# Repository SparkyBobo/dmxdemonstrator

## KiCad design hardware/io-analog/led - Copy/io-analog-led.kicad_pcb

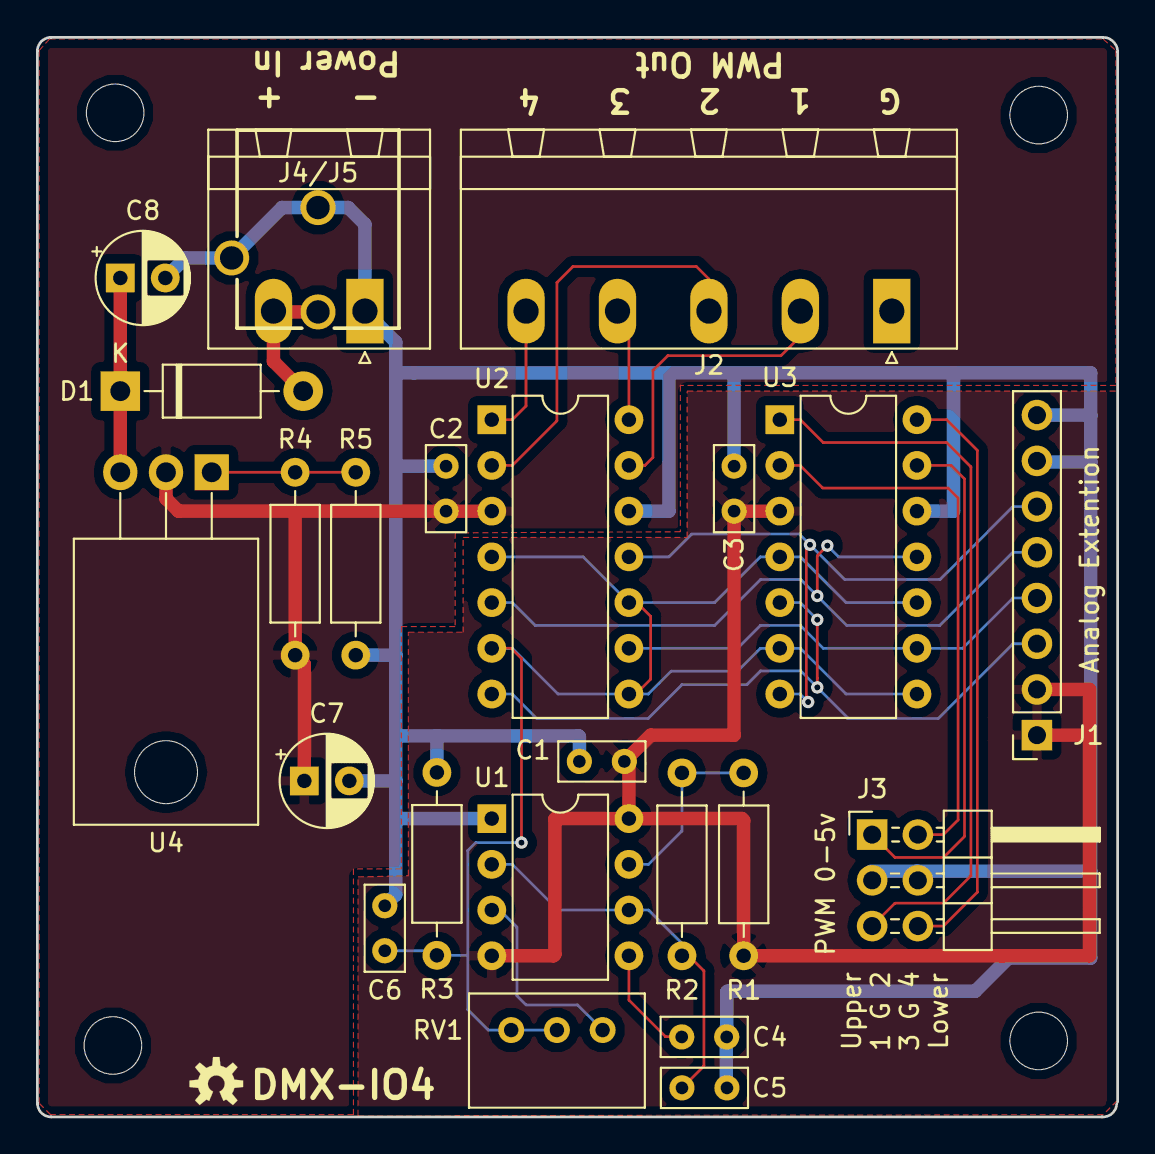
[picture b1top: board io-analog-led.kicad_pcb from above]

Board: 2 copper layers, 60.0 x 60.0 mm, 28 parts (0 on the bottom side), 23 nets.

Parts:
C1, C2, C3: 0.1uF; C_Rect_L4.6mm_W2.0mm_P2.50mm_MKS02_FKP02
C4: 100nf; C_Rect_L4.6mm_W2.0mm_P2.50mm_MKS02_FKP02
C5, C6: 0.68uF; C_Rect_L4.6mm_W2.0mm_P2.50mm_MKS02_FKP02
C7, C8: 10uF; CP_Radial_D5.0mm_P2.50mm
D1: 1N5819; D_DO-41_SOD81_P10.16mm_Horizontal
J1: Analog Extension; PinSocket_1x08_P2.54mm_Vertical
J2: Vo Output; PhoenixContact_MSTBA_2,5_5-G-5,08_1x05_P5.08mm_Horizontal
J3: +5V Output; PinHeader_2x03_P2.54mm_Horizontal
J4: Power; PhoenixContact_MSTBA_2,5_2-G-5,08_1x02_P5.08mm_Horizontal
J5: Power; POWER_JACK_PTH_BREAD
MH1, MH2, MH3, MH4: MountingHole; MountingHole_3.2mm_M3
R1: 330; R_Axial_DIN0207_L6.3mm_D2.5mm_P10.16mm_Horizontal
R2, R3: 10k; R_Axial_DIN0207_L6.3mm_D2.5mm_P10.16mm_Horizontal
R4: 392 1%; R_Axial_DIN0207_L6.3mm_D2.5mm_P10.16mm_Horizontal
R5: 2.74k 1%; R_Axial_DIN0207_L6.3mm_D2.5mm_P10.16mm_Horizontal
RV1: 10k; Potentiometer_Bourns_3299W_Vertical
U1: LM555; DIP-8_W7.62mm
U2, U3: LM339; DIP-14_W7.62mm
U4: LM317T; TO-220-3_Horizontal_TabDown

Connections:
+5V: C1.1, C3.1, J1.1, J1.2, R1.1, U1.4, U1.8, U3.3
/AO0: J1.6, U2.11, U3.7
/AO1: J1.5, U2.5, U3.11
/AO2: J1.4, U2.9, U3.9
/AO3: J1.3, U2.7, U3.5
GND: C1.2, C2.2, C3.2, C4.1, C5.1, C6.2, C7.2, C8.2, J1.7, J1.8, J2.1, J3.3, J3.4, J4.1, J5.GND, J5.GNDB, R3.1, R5.1, U1.1, U2.12, U3.12
unnamed: C2.1, C7.1, R4.2, U2.3, U4.2
unnamed: C4.2, U1.5
unnamed: C5.2, R2.2, U1.2, U1.6
unnamed: C6.1, R3.2, RV1.2, RV1.3, U2.4, U2.6, U2.8, U2.10, U3.4, U3.6, U3.8, U3.10
unnamed: C8.1, D1.1, U4.3
unnamed: D1.2, J4.2, J5.PWR
unnamed: J2.2, U2.13
unnamed: J2.3, U2.2
unnamed: J2.4, U2.14
unnamed: J2.5, U2.1
unnamed: J3.1, U3.13
unnamed: J3.2, U3.2
unnamed: J3.5, U3.1
unnamed: J3.6, U3.14
unnamed: R1.2, R2.1, U1.7
unnamed: R4.1, R5.2, U4.1
unnamed: RV1.1, U1.3

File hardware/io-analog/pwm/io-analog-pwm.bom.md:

# Bill Of Materials (BOM)

## Schematic

**Filename:** E:\OpenSource\dmxdemonstrator\hardware\io-analog\pwm\io-analog-pwm.sch

**Date Modified:** 4/11/2024 8:56:17 PM

**Kicad Version:** Eeschema (5.1.12)-1

**Component Count:** 25

## Components

Item#|Quantity|Reference|Description|Manufacturer|Part Number|Datasheet|Notes
-----|--------|---------|-----------|------------|-----------|---------|-----
1|1|PCB|Analog IO PWM PCB|OHSPark|DMX-IO4, Rev 1.4||[Order](https://oshpark.com/shared_projects/xqcuVAnE)|
2|3|C1, C2, C3|0.1uF||||
3|2|C4, C5|0.68uF||||
4|2|C6, C7|10uF||||
5|1|D1|Schottky Diode, 40V 1A|Vishay General Semiconductor|1N5819|[Data Sheet](http://www.vishay.com/docs/88525/1n5817.pdf)|
6|1|J1|0.1 Female header, stacking||||
7|1|J2|Screw Terminal, 5 pin, 3.81 pitch|Phoenix Contact|1803303||
8|1|J2|Screw Terminal Plug, 5 pin, 3.81 pitch|Phoenix Contact|1840395||
9|1|J3|2x3-pin right-angle header||||
10|1|J4|Screw Terminal, 2 pin, 3.81 pitch|Phoenix Contact|1803277||
11|1|J4|Screw Terminal Plug, 2 pin, 3.81 pitch|Phoenix Contact|1803578||
12|1|R1|330 ohm||||
13|2|R2, R3|10k  ohm||||
14|1|R4|392 ohm 1% resistor||||
15|1|R5|2.74k 1% resistor||||
16|1|RV1|10k trimmer pot|Bourns|3299P-1-103LF|[Data Sheet](https://www.bourns.com/docs/Product-Datasheets/3299.pdf)|
17|1|U1|555 Precision Timer|Texas Instruments|NE555|[Data Sheet](https://www.ti.com/lit/ds/symlink/ne555.pdf)|
18|1|U2|Quad Differential Comparator|Texas Instruments|LM339|[Data Sheet](http://www.ti.com/lit/ds/symlink/lm339.pdf)|
19|1|U3|Linear Regulator, Adjustable, 1.5A TO220AB|STMicroelectronics|LM317T|[Data Sheet](http://www.st.com/content/ccc/resource/technical/document/da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|
<!--BOMROW-->

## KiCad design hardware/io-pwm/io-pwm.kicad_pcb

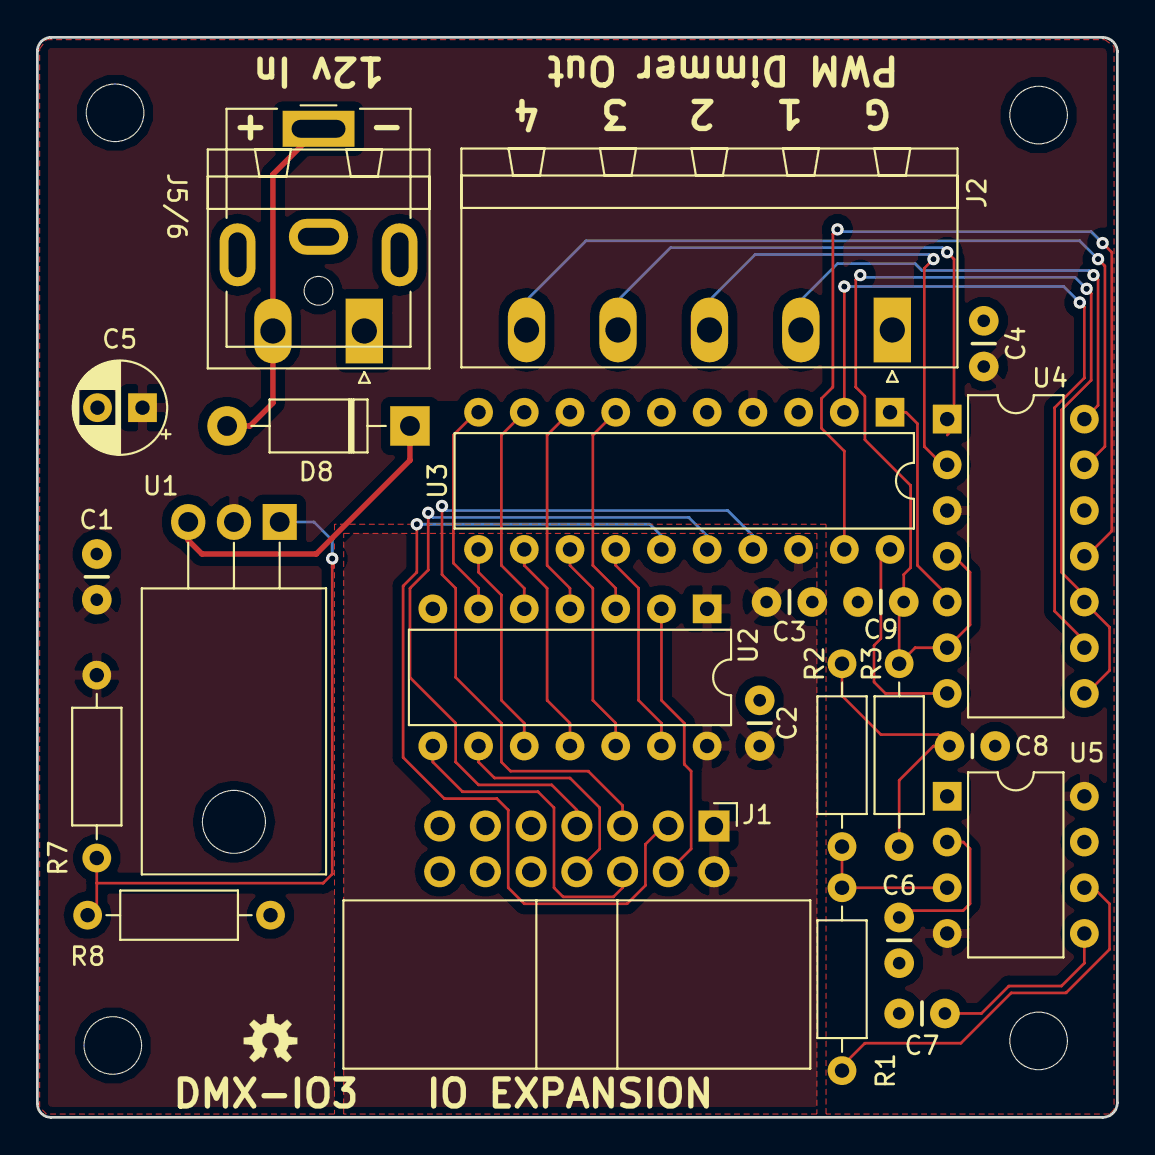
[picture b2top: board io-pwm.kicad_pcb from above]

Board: 2 copper layers, 60.0 x 60.0 mm, 28 parts (0 on the bottom side), 34 nets.

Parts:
C1, C2, C3, C4: .01uF; CAP-PTH-2.54
C5: 10uF; CP_Radial_D5.0mm_P2.50mm
C6, C8, C9: 10nf; CAP-PTH-2.54
C7: 100nf; CAP-PTH-2.54
D8: 1N5819; D_DO-41_SOD81_P10.16mm_Horizontal
J1: IO EXTENSION; IDC-Header_2x07_P2.54mm_Horizontal
J2: PWM_OUT; PhoenixContact_MSTBA_2,5_5-G-5,08_1x05_P5.08mm_Horizontal
J5: 12V_A; BarrelJack_CUI_PJ-063AH_Horizontal
J6: 12V_B; PhoenixContact_MSTBA_2,5_2-G-5,08_1x02_P5.08mm_Horizontal
MH1, MH2, MH3, MH4: MountingHole; MountingHole_3.2mm_M3
R1: 10k; R_Axial_DIN0207_L6.3mm_D2.5mm_P10.16mm_Horizontal
R2, R3: 1k; R_Axial_DIN0207_L6.3mm_D2.5mm_P10.16mm_Horizontal
R7: 390; R_Axial_DIN0207_L6.3mm_D2.5mm_P10.16mm_Horizontal
R8: 2.7k; R_Axial_DIN0207_L6.3mm_D2.5mm_P10.16mm_Horizontal
U1: LM317T; TO-220-3_Horizontal_TabDown
U2: 74LS164; DIP-14_W7.62mm
U3: TLC7226A; DIP-20_W7.62mm
U4: LM339; DIP-14_W7.62mm
U5: LM555; DIP-8_W7.62mm

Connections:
+5V: C2.1, C3.1, J1.1, J1.2, U2.1, U2.14, U3.18
+10V: C1.1, C4.1, C5.1, R7.2, U1.2, U3.4, U4.3, U5.4, U5.8
/A0: J1.5, U3.17
/A1: J1.7, U3.16
/AO0: U3.2, U4.9
/AO1: U3.1, U4.5
/AO2: U3.20, U4.7
/AO3: U3.19, U4.11
/D0: U2.13, U3.14
/D1: U2.12, U3.13
/D2: U2.11, U3.12
/D3: U2.10, U3.11
/D4: U2.6, U3.10
/D5: U2.5, U3.9
/D6: U2.4, U3.8
/D7: U2.3, U3.7
/SR-CLK: J1.6, U2.8
/SR-OUT: J1.4, U2.2
/~SR_CLR: J1.8, U2.9
/~WR: J1.3, U3.15
GND: C1.2, C2.2, C3.2, C4.2, C5.2, C6.1, C7.1, C8.2, C9.2, J1.13, J1.14, J2.1, J5.2, J6.1, R8.1, U2.7, U3.3, U3.5, U3.6, U4.12, U5.1
unnamed: C6.2, U5.2
unnamed: C7.2, U5.5
unnamed: C8.1, R2.1, R3.2
unnamed: C9.1, R3.1, U4.4, U4.6, U4.8, U4.10
unnamed: D8.1, U1.3
unnamed: D8.2, J5.1, J6.2
unnamed: J2.2, U4.14
unnamed: J2.3, U4.2
unnamed: J2.4, U4.1
unnamed: J2.5, U4.13
unnamed: R1.1, U5.6
unnamed: R1.2, R2.2, U5.3
unnamed: R7.1, R8.2, U1.1

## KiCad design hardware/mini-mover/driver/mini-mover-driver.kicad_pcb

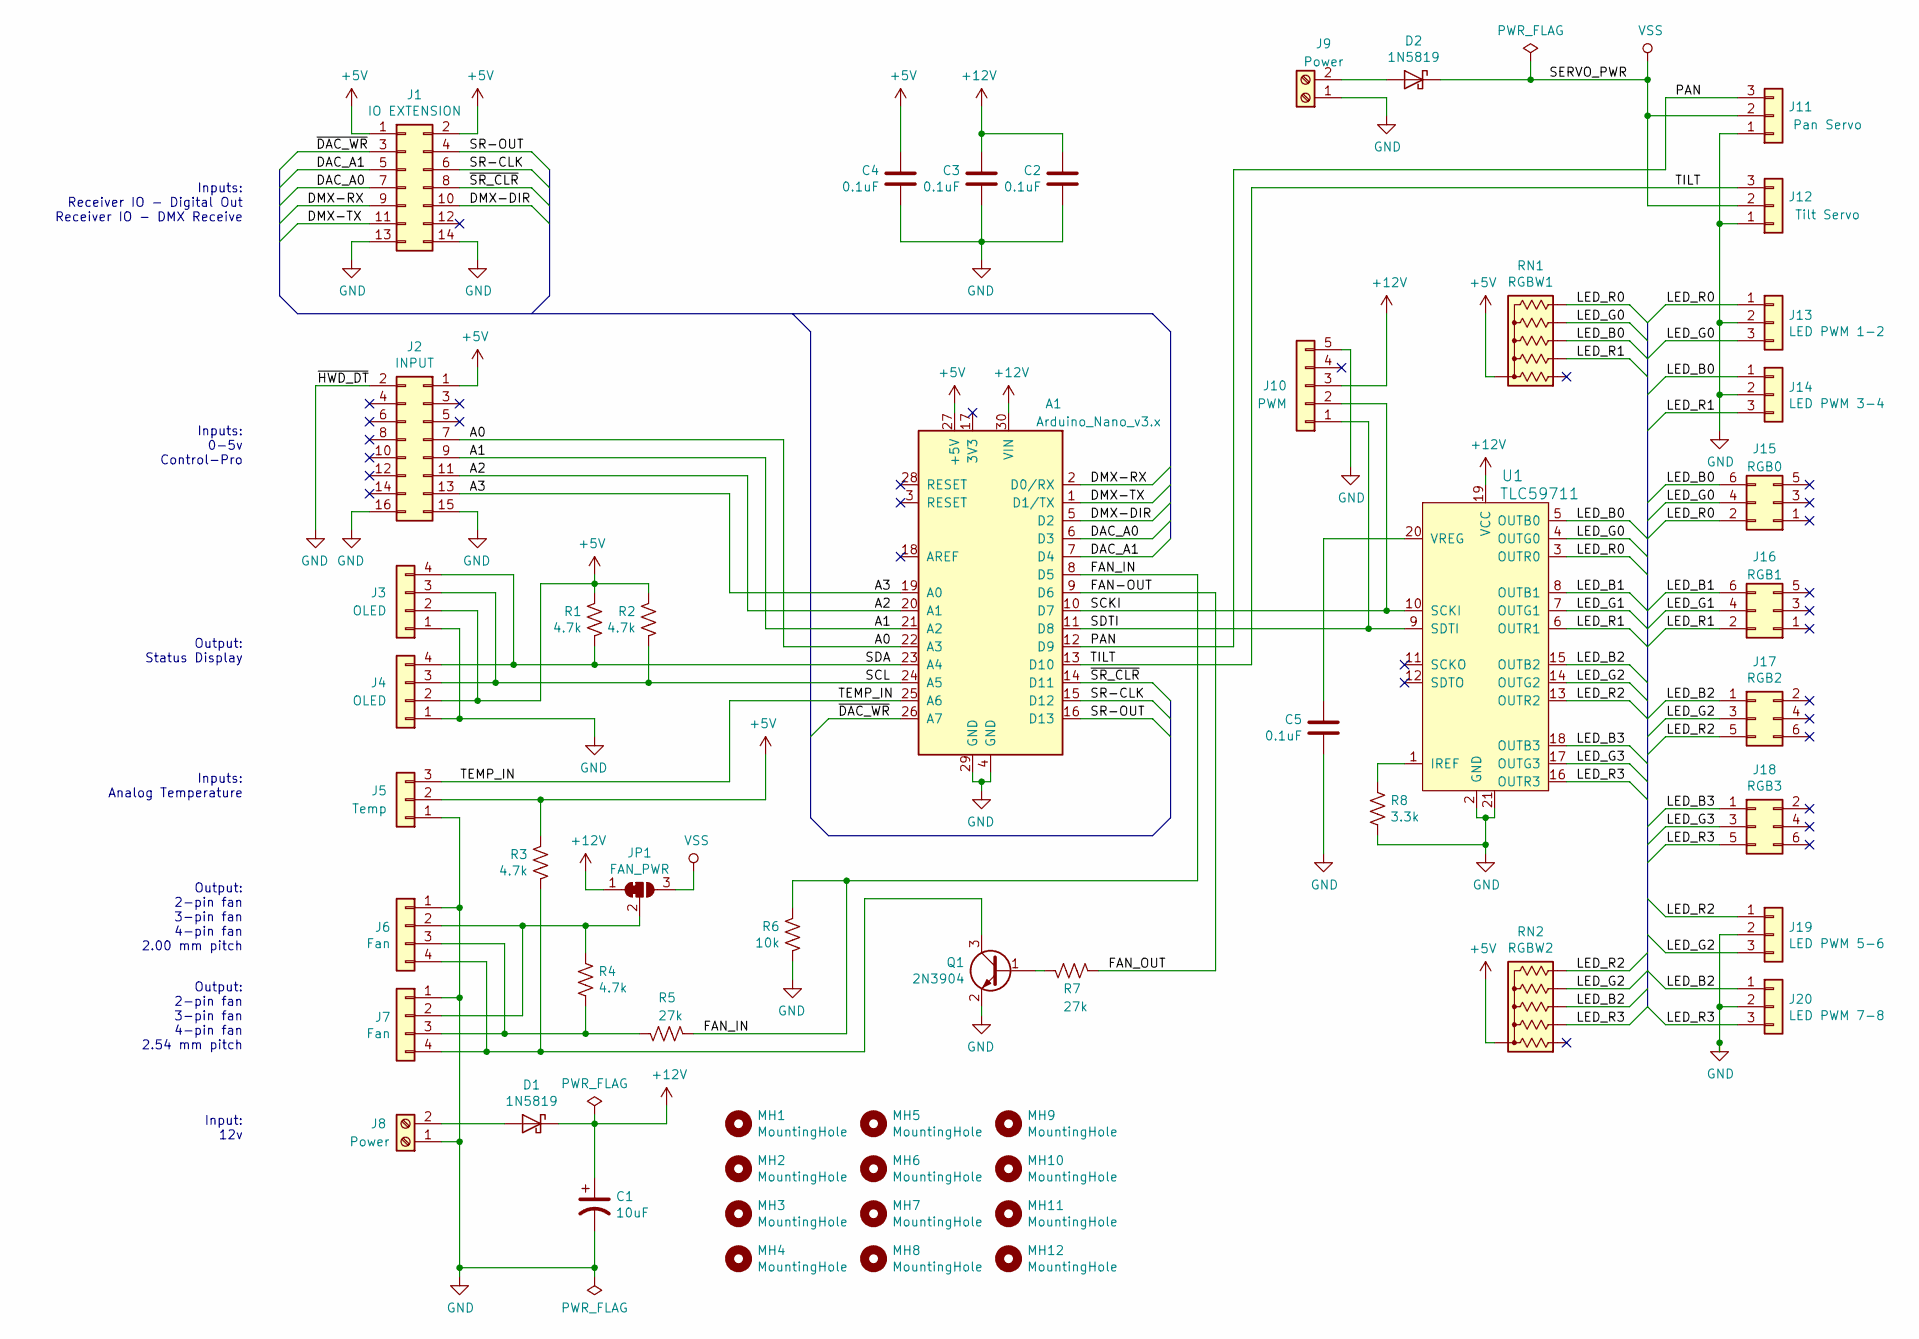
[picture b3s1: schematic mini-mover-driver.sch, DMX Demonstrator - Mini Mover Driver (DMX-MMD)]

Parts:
A1: Arduino_Nano_v3.x; Arduino_Nano
C1: 10uF; CP_Radial_D5.0mm_P2.50mm; Digi-Key_PN P10425CT-ND
C2, C4: 0.1uF; C_Rect_L4.6mm_W2.0mm_P2.50mm_MKS02_FKP02
C3, C5: 0.1uF; C_1206_3216Metric_Pad1.42x1.75mm_HandSolder
D1, D2: 1N5819; D_DO-41_SOD81_P10.16mm_Horizontal; Digi-Key_PN 1N5819-E3/54GITR-ND
J1: IO EXTENSION; IDC-Header_2x07_P2.54mm_Vertical
J2: INPUT; IDC-Header_2x08_P2.54mm_Vertical
J3, J4: OLED; PinHeader_1x04_P2.54mm_Vertical
J5: Temp; PinHeader_1x03_P2.54mm_Vertical
J6: Fan; PinHeader_1x04_P2.00mm_Vertical
J7: Fan; PinHeader_1x04_P2.54mm_Vertical
J8, J9: Power; PhoenixContact_MC_1,5_2-G-3.81_1x02_P3.81mm_Horizontal; Digi-Key_PN 277-1106-ND
J10: PWM; PinHeader_1x05_P2.54mm_Vertical
J11: Pan Servo; PinHeader_1x03_P2.54mm_Vertical
J12: Tilt Servo; PinHeader_1x03_P2.54mm_Vertical
J13: LED PWM 1-2; PinHeader_1x03_P2.54mm_Vertical
J14: LED PWM 3-4; PinHeader_1x03_P2.54mm_Vertical
J15: RGB0; PinHeader_2x03_P2.54mm_Vertical
J16: RGB1; PinHeader_2x03_P2.54mm_Vertical
J17: RGB2; PinHeader_2x03_P2.54mm_Vertical
J18: RGB3; PinHeader_2x03_P2.54mm_Vertical
J19: LED PWM 5-6; PinHeader_1x03_P2.54mm_Vertical
J20: LED PWM 7-8; PinHeader_1x03_P2.54mm_Vertical
JP1: FAN_PWR; SolderJumper-3_P1.3mm_Bridged12_RoundedPad1.0x1.5mm
MH1, MH2, MH3, MH4, MH5, MH6, MH7, MH8: MountingHole; MountingHole_3.2mm_M3
MH9, MH10, MH11, MH12: MountingHole; MountingHole_2.2mm_M2
Q1: 2N3904; TO-92L_HandSolder
R1, R2, R3, R4: 4.7k; R_Axial_DIN0207_L6.3mm_D2.5mm_P10.16mm_Horizontal
R5, R7: 27k; R_Axial_DIN0207_L6.3mm_D2.5mm_P10.16mm_Horizontal
R6: 10k; R_Axial_DIN0207_L6.3mm_D2.5mm_P10.16mm_Horizontal
R8: 3.3k; R_1206_3216Metric_Pad1.42x1.75mm_HandSolder
RN1: RGBW1; R_Array_SIP6
RN2: RGBW2; R_Array_SIP6
U1: TLC59711; TSSOP-20-1EP_W4.4mm; MPN TLC59711PWPR; Digi-Key_PN 296-36745-1-ND

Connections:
+5V: A1.27 (+5V), C4.1, J1.1, J1.2, J2.1, J2.4, J3.2, J4.2, J5.2, R1.1, R2.1, R3.1, RN1.1 (common), RN2.1 (common)
+12V: A1.30 (VIN), C1.1, C2.1, C3.1, D1.1 (K), J10.3, JP1.1 (A), U1.19 (VCC)
/A0: A1.22 (A3), J2.7
/A1: A1.21 (A2), J2.9
/A2: A1.20 (A1), J2.11
/A3: A1.19 (A0), J2.13
/DAC_A0: A1.6 (D3), J1.7
/DAC_A1: A1.7 (D4), J1.5
/DMX-DIR: A1.5 (D2), J1.10
/DMX-RX: A1.2 (D0/RX), J1.9
/DMX-TX: A1.1 (D1/TX), J1.11
/FAN-OUT: A1.9 (D6), R7.1
/FAN_IN: A1.8 (D5), R5.1, R6.1
/LED_B0: J14.1, J15.6, RN1.4 (R3), U1.5 (OUTB0)
/LED_B1: J16.6, U1.8 (OUTB1)
/LED_B2: J17.1, J20.1, RN2.4 (R3), U1.15 (OUTB2)
/LED_B3: J18.1, U1.18 (OUTB3)
/LED_G0: J13.3, J15.4, RN1.5 (R4), U1.4 (OUTG0)
/LED_G1: J16.4, U1.7 (OUTG1)
/LED_G2: J17.3, J19.3, RN2.5 (R4), U1.14 (OUTG2)
/LED_G3: J18.3, U1.17 (OUTG3)
/LED_R0: J13.1, J15.2, RN1.6 (R5), U1.3 (OUTR0)
/LED_R1: J14.3, J16.2, RN1.3 (R2), U1.6 (OUTR1)
/LED_R2: J17.5, J19.1, RN2.6 (R5), U1.13 (OUTR2)
/LED_R3: J18.5, J20.3, RN2.3 (R2), U1.16 (OUTR3)
/PAN: A1.12 (D9), J11.3
/SCKI: A1.10 (D7), J10.2, U1.10 (SCKI)
/SCL: A1.24 (A5), J3.3, J4.3, R2.2
/SDA: A1.23 (A4), J3.4, J4.4, R1.2
/SDTI: A1.11 (D8), J10.1, U1.9 (SDTI)
/SR-CLK: A1.15 (D12), J1.6
/SR-OUT: A1.16 (D13), J1.4
/TEMP_IN: A1.25 (A6), J5.3
/TILT: A1.13 (D10), J12.3
/~DAC_WR: A1.26 (A7), J1.3
/~SR_CLR: A1.14 (D11), J1.8
GND: A1.4 (GND), A1.29 (GND), C1.2, C2.2, C3.2, C4.2, C5.2, J1.13, J1.14, J2.2, J2.8, J2.15, J2.16, J3.1, J4.1, J5.1, J6.1, J7.1, J8.1, J9.1, J10.5, J11.1, J12.1, J13.2, J14.2, J19.2, J20.2, Q1.2 (E), R6.2, R8.2, U1.2 (GND), U1.21
unnamed: C5.1, U1.20 (VREG)
unnamed: D1.2 (A), J8.2
unnamed: D2.2 (A), J9.2
unnamed: J6.2, J7.2, JP1.2 (C), R4.1
unnamed: J6.3, J7.3, R4.2, R5.2
unnamed: J6.4, J7.4, Q1.3 (C), R3.2
unnamed: Q1.1 (B), R7.2
unnamed: R8.1, U1.1 (IREF)
VSS: D2.1 (K), J11.2, J12.2, JP1.3 (B)

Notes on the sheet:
Inputs: Receiver IO - Digital Out Receiver IO - DMX Receive
Inputs: 0-5v Control-Pro
Inputs: Analog Temperature
Output: 2-pin fan 3-pin fan 4-pin fan 2.00 mm pitch
Output: 2-pin fan 3-pin fan 4-pin fan 2.54 mm pitch
Input: 12v
Output: Status Display

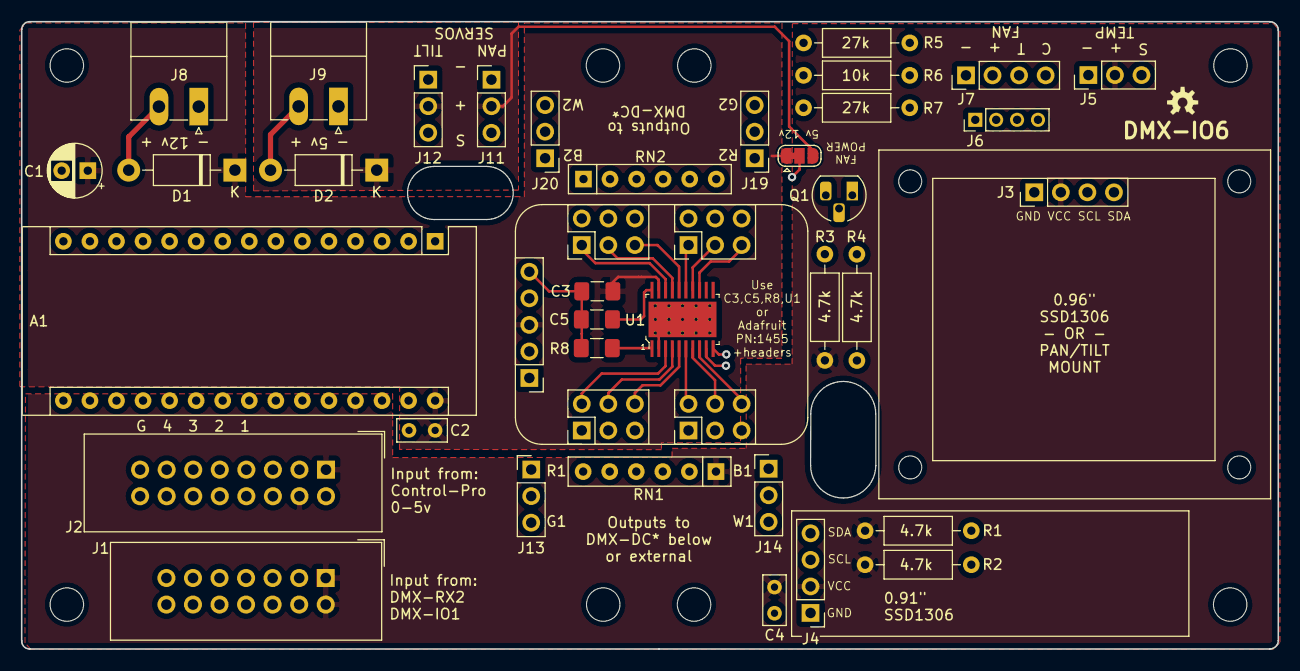
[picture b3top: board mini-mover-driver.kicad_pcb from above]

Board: 4 copper layers, 120.2 x 60.0 mm, 53 parts (0 on the bottom side), 46 nets.

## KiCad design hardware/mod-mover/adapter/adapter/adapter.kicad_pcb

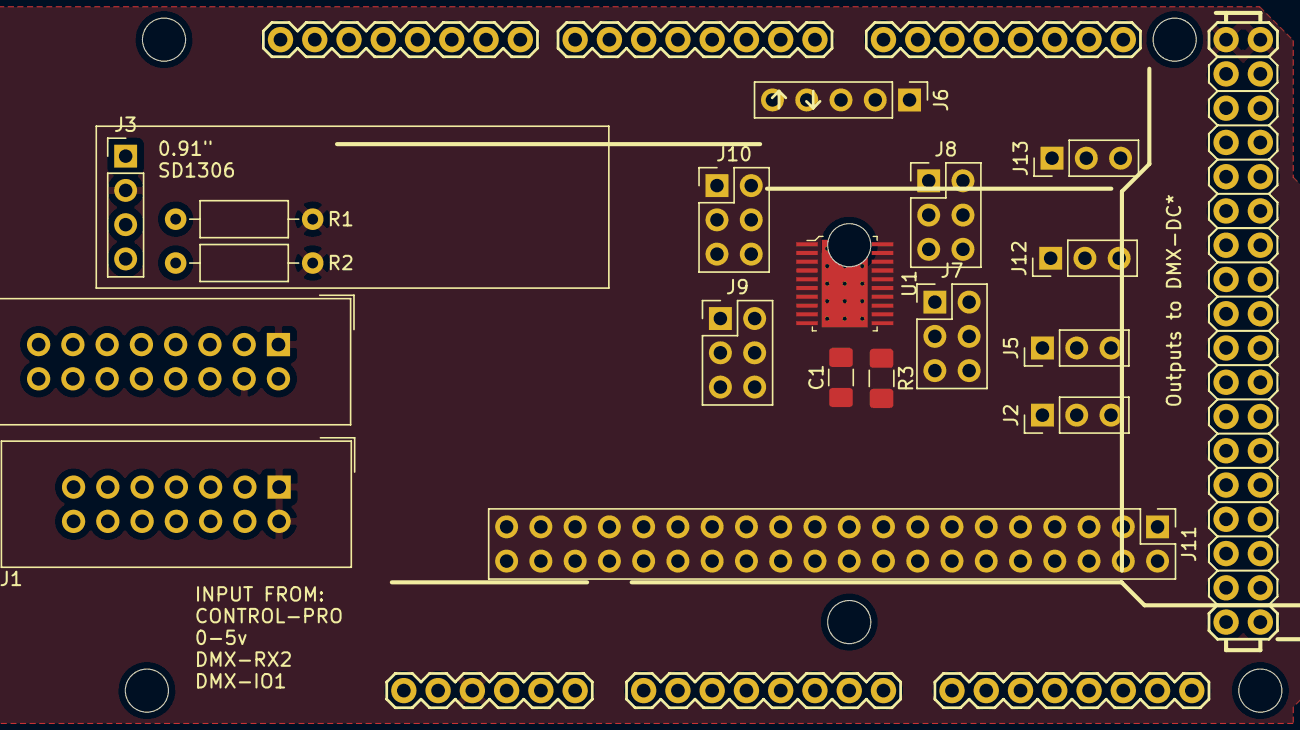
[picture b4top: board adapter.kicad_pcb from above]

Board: 2 copper layers, 19 parts (0 on the bottom side), 58 nets, no tracks yet.

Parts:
B1: ARDUINO_MEGA_R3FULL; ARDUINO_MEGA
C1: 0.1uF; C_1206_3216Metric_Pad1.42x1.75mm_HandSolder
J1: IO EXTENSION; IDC-Header_2x07_P2.54mm_Vertical
J2: LED PWM 1-2; PinHeader_1x03_P2.54mm_Vertical
J3: OLED; PinHeader_1x04_P2.54mm_Vertical
J4: INPUT; IDC-Header_2x08_P2.54mm_Vertical
J5: LED PWM 3-4; PinHeader_1x03_P2.54mm_Vertical
J6: PWM; PinHeader_1x05_P2.54mm_Vertical
J7: RGB0; PinHeader_2x03_P2.54mm_Vertical
J8: RGB1; PinHeader_2x03_P2.54mm_Vertical
J9: RGB2; PinHeader_2x03_P2.54mm_Vertical
J10: RGB3; PinHeader_2x03_P2.54mm_Vertical
J11: MV EXTENSION; PinHeader_2x20_P2.54mm_Vertical
J12: LED PWM 5-6; PinHeader_1x03_P2.54mm_Vertical
J13: LED PWM 7-8; PinHeader_1x03_P2.54mm_Vertical
R1, R2: 4.7k; R_Axial_DIN0207_L6.3mm_D2.5mm_P10.16mm_Horizontal
R3: 3.3k; R_1206_3216Metric_Pad1.42x1.75mm_HandSolder
U1: TLC59711; TSSOP-20-1EP_W4.4mm

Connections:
+5V: B1.5V@0, B1.5V@1, B1.5V@2, J1.1, J1.2, J3.2, J4.1, J11.1, J11.2, R1.1, R2.1
+12V: J6.3, U1.19
/A0: B1.A8, J4.7
/A1: B1.A9, J4.9
/A2: B1.A10, J4.11
/A3: B1.A11, J4.13
/DAC_A0: B1.27, J1.7
/DAC_A1: B1.26, J1.5
/DMX-DIR: B1.2, J1.10
/DMX-RX: B1.0, J1.9
/DMX-TX: B1.1, J1.11
/FAN0: B1.44, J11.18
/FAN1: B1.45, J11.20
/FAN2: B1.46, J11.22
/FANSP0: B1.13, J11.12
/FANSP1: B1.14, J11.14
/FANSP2: B1.15, J11.16
/LED_B0: J5.1, J7.6, J11.11, U1.5
/LED_B1: J8.6, U1.8
/LED_B2: J9.1, J11.19, J13.1, U1.15
/LED_B3: J10.1, U1.18
/LED_G0: J2.3, J7.4, J11.9, U1.4
/LED_G1: J8.4, U1.7
/LED_G2: J9.3, J11.17, J12.3, U1.14
/LED_G3: J10.3, U1.17
/LED_R0: J2.1, J7.2, J11.7, U1.3
/LED_R1: J5.3, J8.2, J11.13, U1.6
/LED_R2: J9.5, J11.15, J12.1, U1.13
/LED_R3: J10.5, J11.21, J13.3, U1.16
/MTR0A: B1.9, J11.30
/MTR0B: B1.10, J11.32
/MTR0C: B1.4, J11.33
/MTR1A: B1.11, J11.34
/MTR1B: B1.12, J11.36
/MTR1C: B1.5, J11.35
/PAN: B1.6, J11.24
/SCKI0: B1.16, J6.2, U1.10
/SCL: B1.21, J3.3, J11.3, R1.2
/SDA: B1.20, J3.4, J11.5, R2.2
/SDTI0: B1.17, J6.1, U1.9
/SERVO2: B1.8, J11.28
/SR-CLK: B1.23, J1.6
/SR-OUT: B1.22, J1.4
/SW0: B1.39, J11.23
/SW1: B1.40, J11.25
/SW2: B1.41, J11.27
/SW3: B1.42, J11.29
/SW4: B1.43, J11.31
/TEMP1: B1.A4, J11.4
/TEMP2: B1.A5, J11.6
/TEMP3: B1.A6, J11.8
/TEMP4: B1.A7, J11.10
/TILT: B1.7, J11.26
/~DAC_WR: B1.25, J1.3
/~SR_CLR: B1.24, J1.8
GND: B1.GND@, C1.2, J1.13, J1.14, J2.2, J3.1, J4.2, J4.8, J4.15, J4.16, J5.2, J6.5, J11.37, J11.38, J11.39, J11.40, J12.2, J13.2, R3.2, U1.2, U1.21
unnamed: C1.1, U1.20
unnamed: R3.1, U1.1

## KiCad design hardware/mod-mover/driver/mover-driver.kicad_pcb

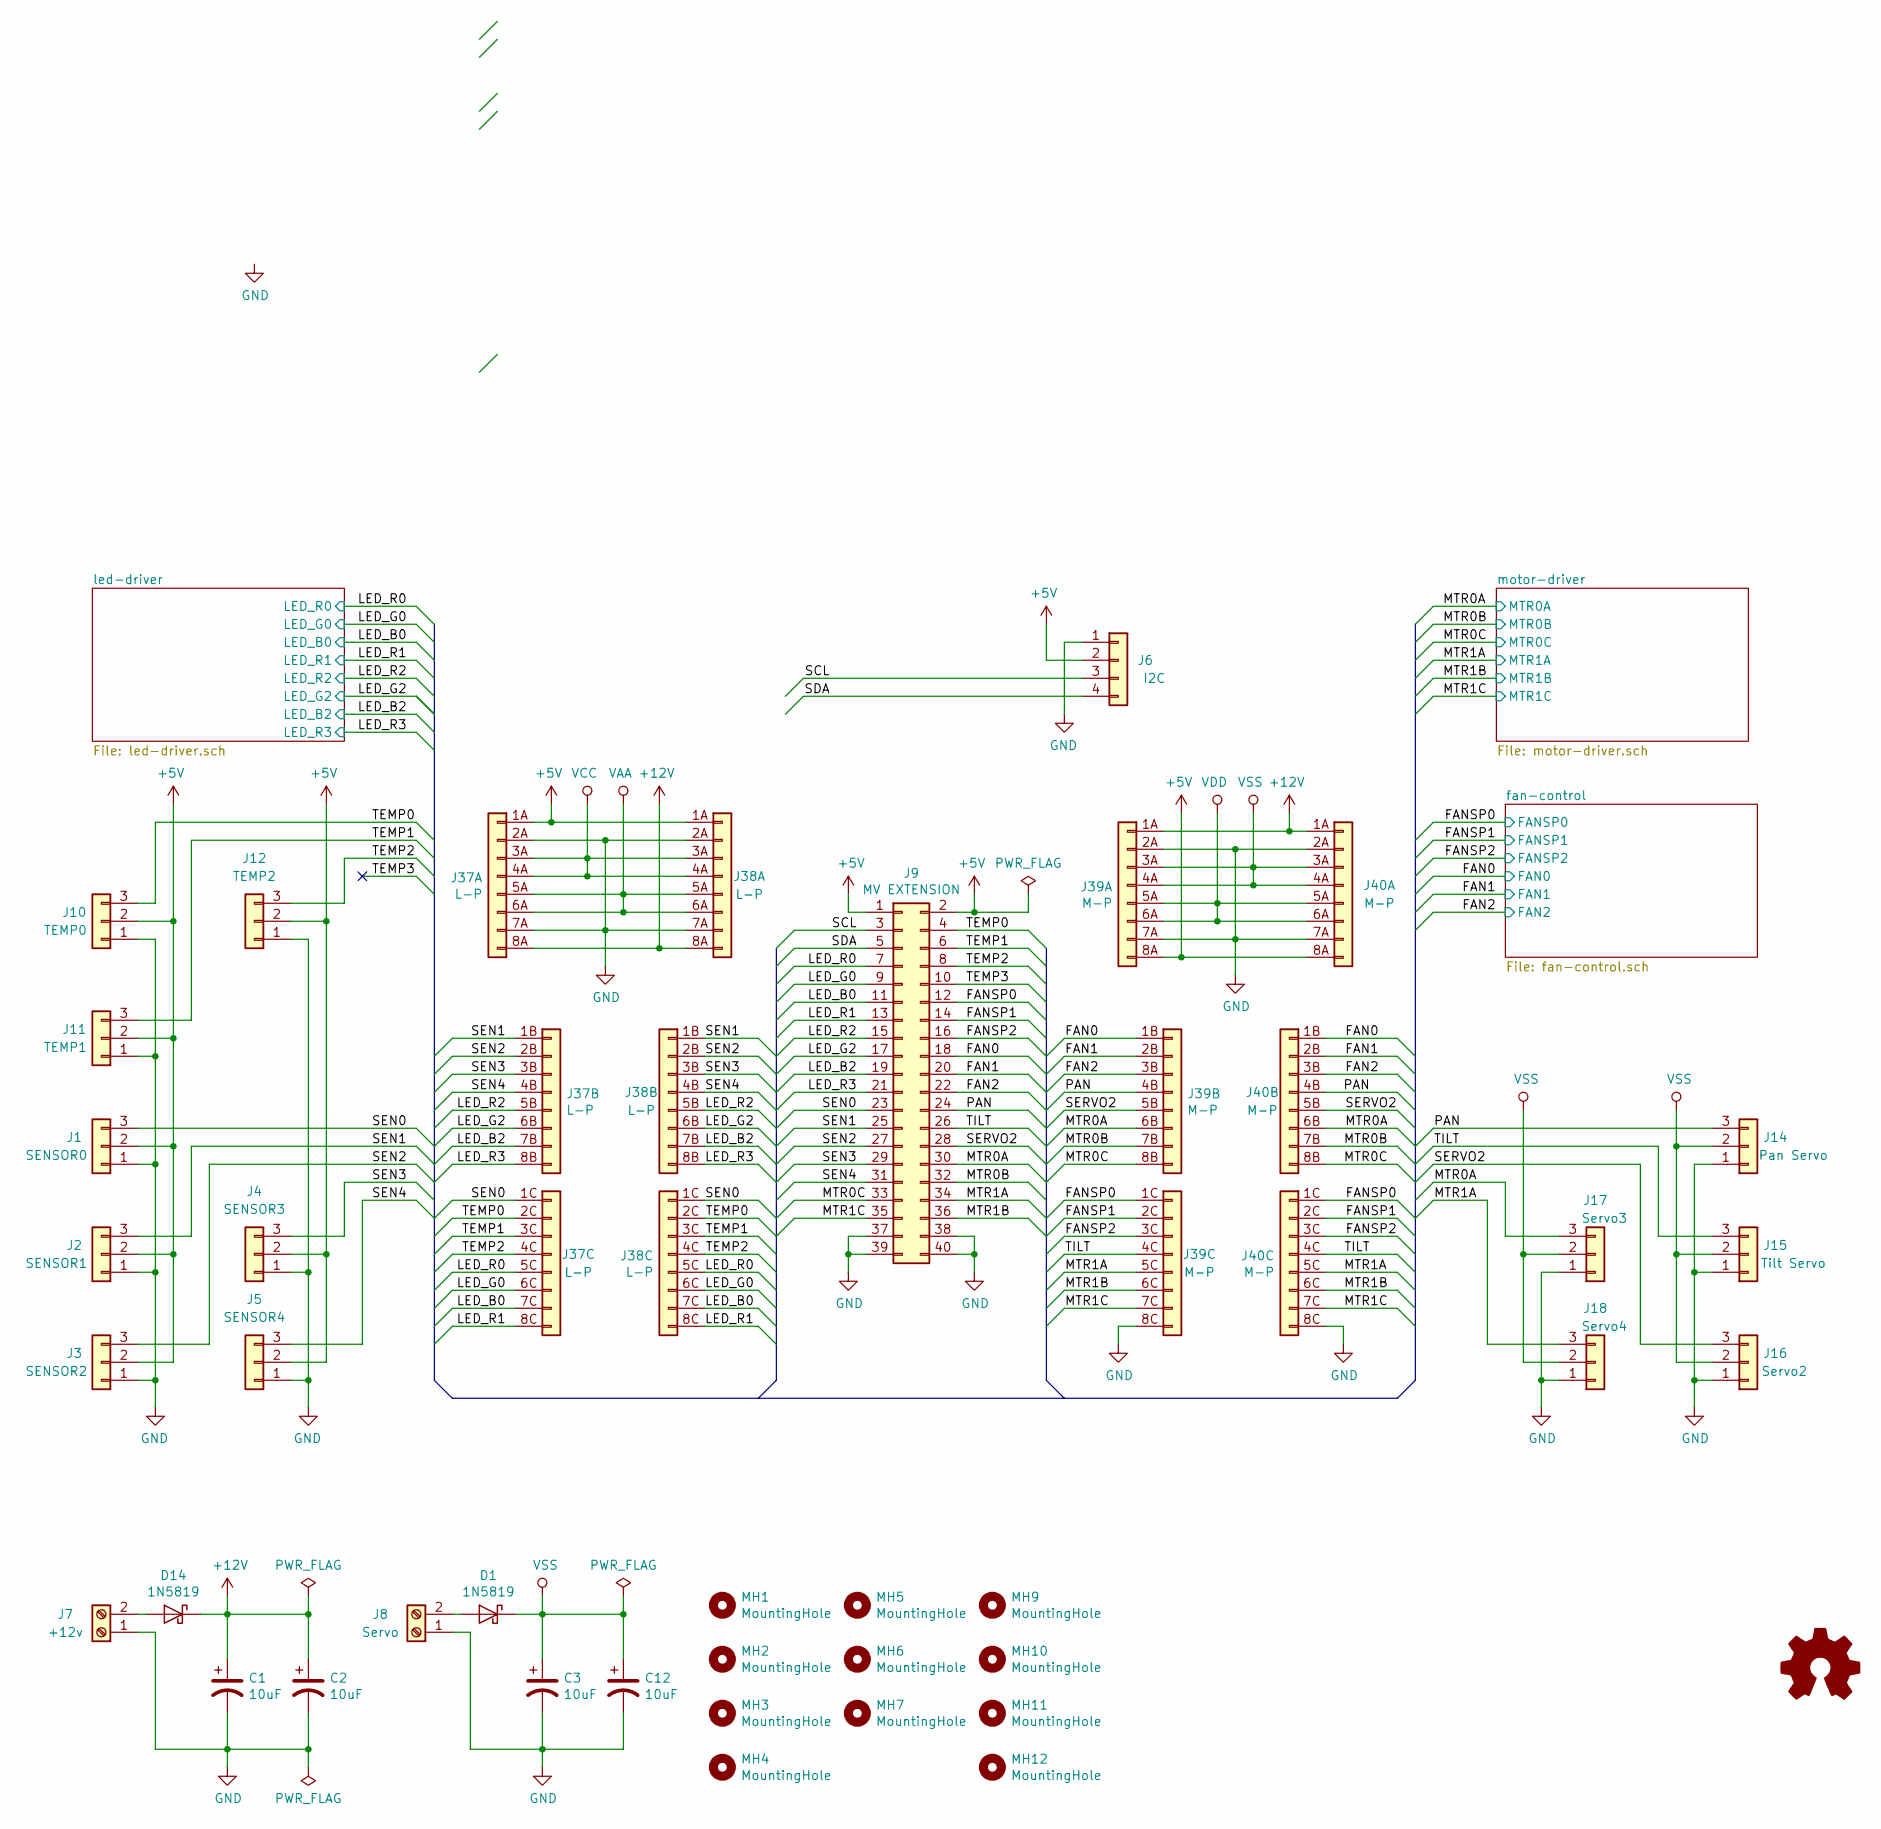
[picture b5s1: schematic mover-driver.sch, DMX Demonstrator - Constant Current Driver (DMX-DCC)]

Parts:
C1, C2, C3, C12: 10uF; C_1206_3216Metric_Pad1.42x1.75mm_HandSolder; Digi-Key_PN P10425CT-ND
D1, D14: 1N5819; D_SOD-123F; Digi-Key_PN 1N5819-E3/54GITR-ND
J1: SENSOR0; PinHeader_1x03_P2.54mm_Vertical
J2: SENSOR1; PinHeader_1x03_P2.54mm_Vertical
J3: SENSOR2; PinHeader_1x03_P2.54mm_Vertical
J4: SENSOR3; PinHeader_1x03_P2.54mm_Vertical
J5: SENSOR4; PinHeader_1x03_P2.54mm_Vertical
J6: I2C; PinHeader_1x04_P2.54mm_Vertical
J7: +12v; PhoenixContact_MCV_1,5_2-G-3.81_1x02_P3.81mm_Vertical
J8: Servo; PhoenixContact_MCV_1,5_2-G-3.81_1x02_P3.81mm_Vertical; Digi-Key_PN 277-1106-ND
J9: MV EXTENSION; PinHeader_2x20_P2.54mm_Vertical
J10: TEMP0; PinHeader_1x03_P2.54mm_Vertical
J11: TEMP1; PinHeader_1x03_P2.54mm_Vertical
J12: TEMP2; PinHeader_1x03_P2.54mm_Vertical
J14: Pan Servo; PinHeader_1x03_P2.54mm_Vertical
J15: Tilt Servo; PinHeader_1x03_P2.54mm_Vertical
J16: Servo2; PinHeader_1x03_P2.54mm_Vertical
J17: Servo3; PinHeader_1x03_P2.54mm_Vertical
J18: Servo4; PinHeader_1x03_P2.54mm_Vertical
J37: L-P; PinHeader_3x08_P2.54mm_Vertical
J38: L-P; PinSocket_3x08_P2.54mm_Horizontal
J39: M-P; PinSocket_3x08_P2.54mm_Horizontal
J40: M-P; PinHeader_3x08_P2.54mm_Vertical
MH1, MH2, MH3, MH4, MH5, MH6, MH7, MH9, MH10, MH11, MH12: MountingHole; MountingHole_4.3mm_M4

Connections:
+5V: J1.2, J2.2, J3.2, J4.2, J5.2, J6.2, J9.1, J9.2, J10.2, J11.2, J12.2, J37.1A, J38.1A, J39.8A, J40.8A; also elsewhere on the board
+12V: C1.1, C2.1, D14.1 (K), J37.8A, J38.8A, J39.1A, J40.1A; also elsewhere on the board
/FAN0: J9.18, J39.1B, J40.1B; also elsewhere on the board
/FAN1: J9.20, J39.2B, J40.2B; also elsewhere on the board
/FAN2: J9.22, J39.3B, J40.3B; also elsewhere on the board
/FANSP0: J9.12, J39.1C, J40.1C; also elsewhere on the board
/FANSP1: J9.14, J39.2C, J40.2C; also elsewhere on the board
/FANSP2: J9.16, J39.3C, J40.3C; also elsewhere on the board
/LED_B0: J9.11, J37.7C, J38.7C; also elsewhere on the board
/LED_B2: J9.19, J37.7B, J38.7B; also elsewhere on the board
/LED_G0: J9.9, J37.6C, J38.6C; also elsewhere on the board
/LED_G2: J9.17, J37.6B, J38.6B; also elsewhere on the board
/LED_R0: J9.7, J37.5C, J38.5C; also elsewhere on the board
/LED_R1: J9.13, J37.8C, J38.8C; also elsewhere on the board
/LED_R2: J9.15, J37.5B, J38.5B; also elsewhere on the board
/LED_R3: J9.21, J37.8B, J38.8B; also elsewhere on the board
/MTR0A: J9.30, J17.3, J39.6B, J40.6B; also elsewhere on the board
/MTR0B: J9.32, J39.7B, J40.7B; also elsewhere on the board
/MTR0C: J9.33, J39.8B, J40.8B; also elsewhere on the board
/MTR1A: J9.34, J18.3, J39.5C, J40.5C; also elsewhere on the board
/MTR1B: J9.36, J39.6C, J40.6C; also elsewhere on the board
/MTR1C: J9.35, J39.7C, J40.7C; also elsewhere on the board
/PAN: J9.24, J14.3, J39.4B, J40.4B
/SCL: J6.3, J9.3
/SDA: J6.4, J9.5
/SEN0: J1.3, J9.23, J37.1C, J38.1C
/SEN1: J2.3, J9.25, J37.1B, J38.1B
/SEN2: J3.3, J9.27, J37.2B, J38.2B
/SEN3: J4.3, J9.29, J37.3B, J38.3B
/SEN4: J5.3, J9.31, J37.4B, J38.4B
/SERVO2: J9.28, J16.3, J39.5B, J40.5B
/TEMP0: J9.4, J10.3, J37.2C, J38.2C
/TEMP1: J9.6, J11.3, J37.3C, J38.3C
/TEMP2: J9.8, J12.3, J37.4C, J38.4C
/TILT: J9.26, J15.3, J39.4C, J40.4C
GND: C1.2, C2.2, C3.2, C12.2, J1.1, J2.1, J3.1, J4.1, J5.1, J6.1, J7.1, J8.1, J9.37, J9.38, J9.39, J9.40, J10.1, J11.1, J12.1, J14.1, J15.1, J16.1, J17.1, J18.1, J37.2A, J37.7A, J38.2A, J38.7A, J39.2A, J39.7A, J39.8C, J40.2A, J40.7A, J40.8C; also elsewhere on the board
unnamed: D1.2 (A), J8.2
unnamed: D14.2 (A), J7.2
VAA: J37.5A, J37.6A, J38.5A, J38.6A; also elsewhere on the board
VCC: J37.3A, J37.4A, J38.3A, J38.4A; also elsewhere on the board
VDD: J39.5A, J39.6A, J40.5A, J40.6A; also elsewhere on the board
VSS: C3.1, C12.1, D1.1 (K), J14.2, J15.2, J16.2, J17.2, J18.2, J39.3A, J39.4A, J40.3A, J40.4A

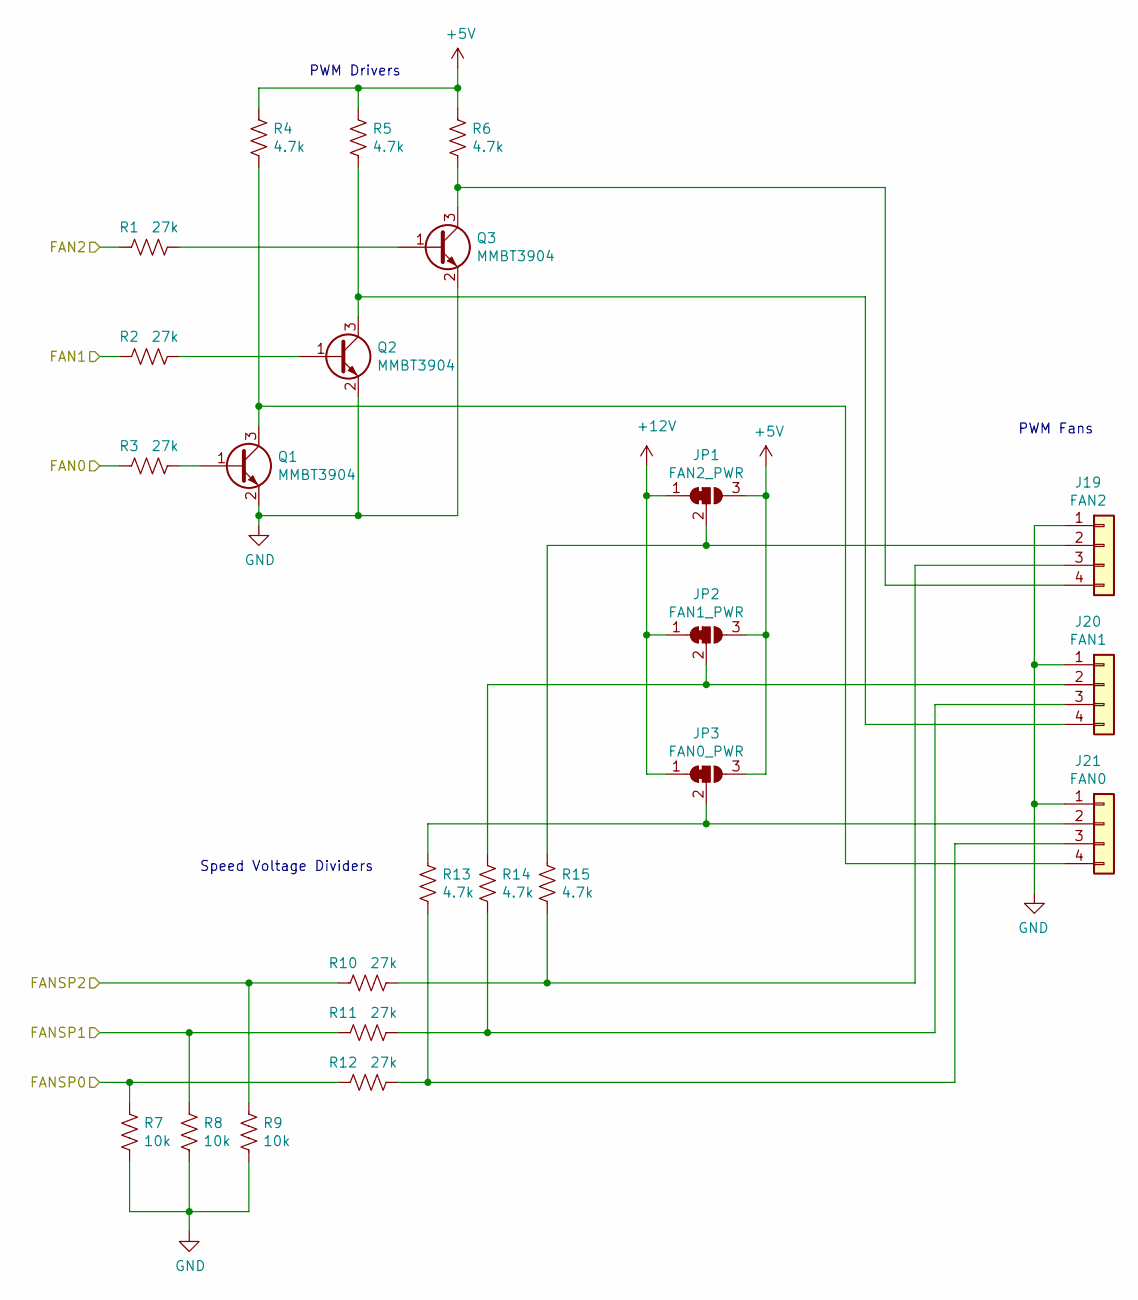
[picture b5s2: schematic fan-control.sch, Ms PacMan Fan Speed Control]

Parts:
J19: FAN2; PinHeader_1x04_P2.54mm_Vertical
J20: FAN1; PinHeader_1x04_P2.54mm_Vertical
J21: FAN0; PinHeader_1x04_P2.54mm_Vertical
JP1: FAN2_PWR; SolderJumper-3_P1.3mm_Bridged12_RoundedPad1.0x1.5mm
JP2: FAN1_PWR; SolderJumper-3_P1.3mm_Bridged12_RoundedPad1.0x1.5mm
JP3: FAN0_PWR; SolderJumper-3_P1.3mm_Bridged12_RoundedPad1.0x1.5mm
Q1, Q2, Q3: MMBT3904; SOT-23
R1, R2, R3, R10, R11, R12: 27k; R_0603_1608Metric_Pad1.05x0.95mm_HandSolder
R4, R5, R6, R13, R14, R15: 4.7k; R_0603_1608Metric_Pad1.05x0.95mm_HandSolder
R7, R8, R9: 10k; R_0603_1608Metric_Pad1.05x0.95mm_HandSolder

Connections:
+5V: JP1.3 (B), JP2.3 (B), JP3.3 (B), R4.1, R5.1, R6.1; also elsewhere on the board
+12V: JP1.1 (A), JP2.1 (A), JP3.1 (A); also elsewhere on the board
/FAN0: R3.1; also elsewhere on the board
/FAN1: R2.1; also elsewhere on the board
/FAN2: R1.1; also elsewhere on the board
/FANSP0: R7.1, R12.1; also elsewhere on the board
/FANSP1: R8.1, R11.1; also elsewhere on the board
/FANSP2: R9.1, R10.1; also elsewhere on the board
GND: J19.1, J20.1, J21.1, Q1.2 (E), Q2.2 (E), Q3.2 (E), R7.2, R8.2, R9.2; also elsewhere on the board
unnamed: J19.2, JP1.2 (C), R15.1
unnamed: J19.3, R10.2, R15.2
unnamed: J19.4, Q3.3 (C), R6.2
unnamed: J20.2, JP2.2 (C), R14.1
unnamed: J20.3, R11.2, R14.2
unnamed: J20.4, Q2.3 (C), R5.2
unnamed: J21.2, JP3.2 (C), R13.1
unnamed: J21.3, R12.2, R13.2
unnamed: J21.4, Q1.3 (C), R4.2
unnamed: Q1.1 (B), R3.2
unnamed: Q2.1 (B), R2.2
unnamed: Q3.1 (B), R1.2

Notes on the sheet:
PWM Fans
Speed Voltage Dividers
PWM Drivers

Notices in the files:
hardware/io-analog/led - Copy/io-analog-led.kicad_pcb:
Released under the Creative Commons Attribution Share-Alike 4.0m License
hardware/mini-mover/driver/mini-mover-driver.kicad_pcb:
Released under the Creative Commons Attribution Share-Alike 4.0 License
hardware/mini-mover/driver/mini-mover-driver.sch:
https://creativecommons.org/licenses/by-sa/4.0
